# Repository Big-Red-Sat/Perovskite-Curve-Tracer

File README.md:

# Perovskite Curve Tracer
This project contains the hardware and software source for the curve tracer developed to evaluate perovskite solar cell samples during the [Big Red Sat-1 project](https://github.com/Big-Red-Sat/Big-Red-Sat-1).

## Hardware
The hardware is licensed under a CERN Open Hardware Licence Version 2 - Strongly Reciprocal license.  The developed hardware performs a passive curve tracing process that utilizes a low-Ohm resistor ladder, realized through analog switches and precision resistors.  The multiplexing of the perovskite solar cells is achieved through a low-Ohm analog SPDT relay.  Provisions are also made for an I2C connection to a temperature sensor on the sample holder.  A simple control interface is provisioned through USB for controlling the hardware and retrieve readings.

## Software
The software is licensed under an MIT license.  The software is operated using a single Python script under the software directory, `curve_tracer.py`.  
1. Clone this repository to a local directory,
2. Create a Python 3.9 virtual environment in the software folder,
3. Install all packages using the requirements.txt file,
4. Run curve_tracer.py.

## Performance
The collected data can be saved to the software folder under a directory called curves.  In that folder are numerous experiments from the Big Red Sat-1 project.  The plotted curves will look like the image below.

## Citation
If this repository was useful to your research, then please cite this repository using the BibTeX definition below.
```
@software{
  Arce_Perovskite_Curve_Tracer_2023,
  author = {Arce, Walker},
  month = aug,
  title = {{Perovskite Curve Tracer}},
  url = {https://github.com/wsarce/Perovskite-Curve-Tracer},
  version = {v1.0.0},
  year = {2023}
}
```
## Contact
For additional information or questions, please contact Walker Arce (wsarcera@gmail.com).

## License
The hardware is licensed under a CERN Open Hardware Licence Version 2 - Strongly Reciprocal, the software and firmware is licensed under an MIT license, and the documentation is licensed under a Creative Commons Attribution-ShareAlike 4.0 International Public License.

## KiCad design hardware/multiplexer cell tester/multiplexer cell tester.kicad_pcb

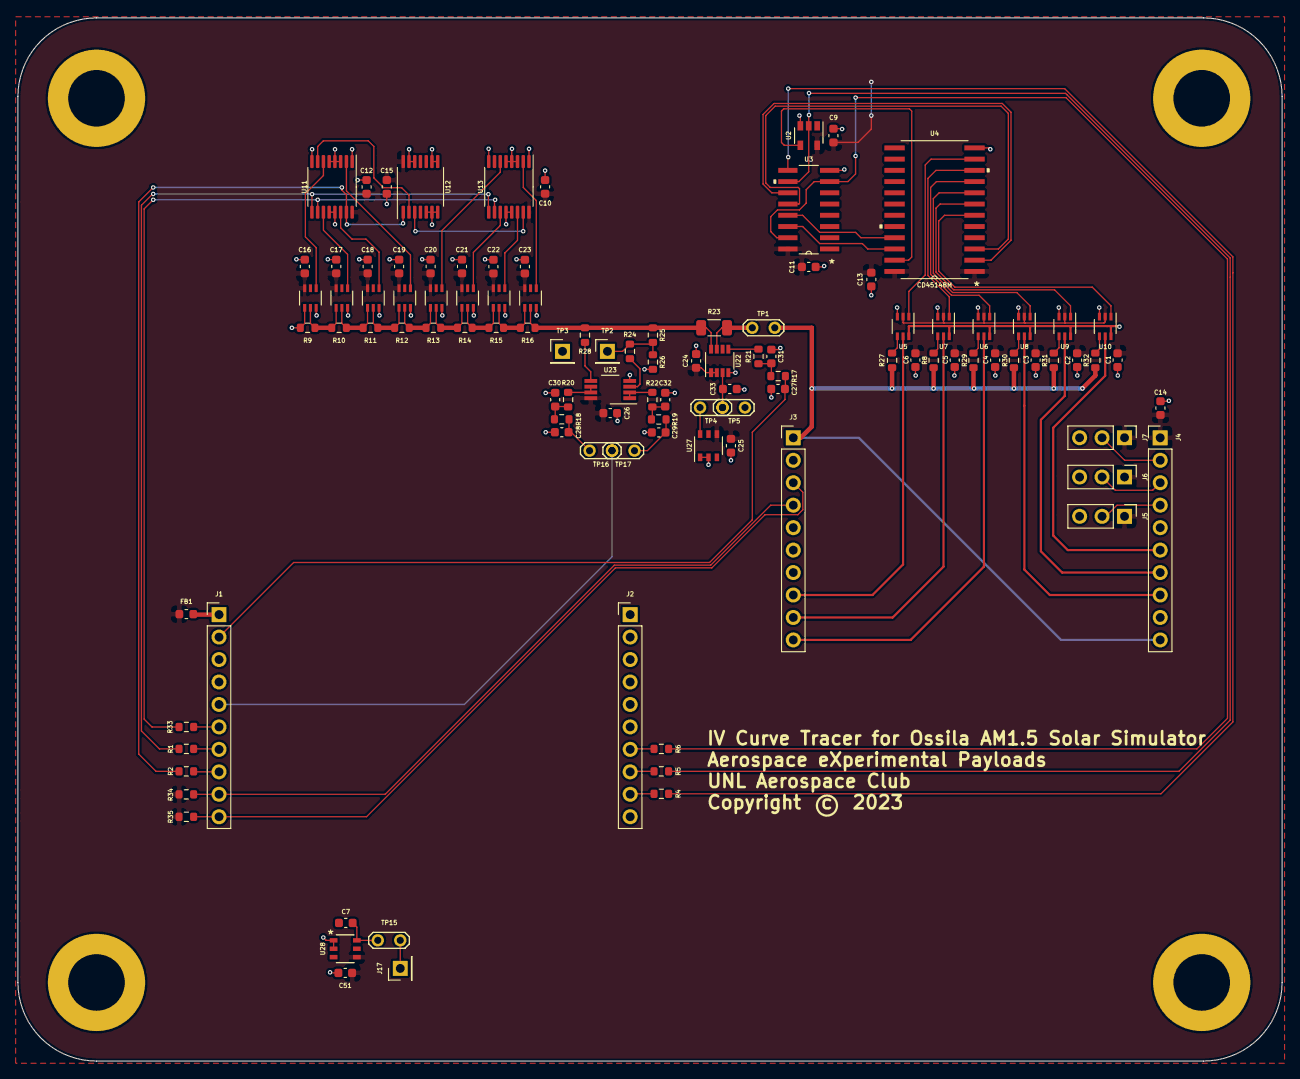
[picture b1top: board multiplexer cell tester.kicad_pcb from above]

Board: 2 copper layers, 143.0 x 118.0 mm, 107 parts (0 on the bottom side), 80 nets.

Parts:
C1, C2, C3, C4, C5, C6, C9, C10, C11, C12, C13, C14, C15, C16, C17, C18, C19, C20, C21, C22, C23, C24, C26, C51: 0.1u; C_0603_1608Metric
C7, C25, C33: 1u; C_0603_1608Metric
C27, C28, C29: 10n; C_0603_1608Metric
C30, C31, C32: 10u; C_0603_1608Metric
FB1: Ferrite_Bead; L_0603_1608Metric
J1, J2, J3, J4: Conn_01x10_Female; PinHeader_1x10_P2.54mm_Vertical
J5: A2 Select; PinHeader_1x03_P2.54mm_Vertical
J6: A1 Select; PinHeader_1x03_P2.54mm_Vertical
J7: A0 Select; PinHeader_1x03_P2.54mm_Vertical
J17: Conn_01x01_Male; PinHeader_1x01_P2.54mm_Vertical
R1, R2, R4, R5, R6, R33: 100; R_0603_1608Metric
R8, R27, R29, R30, R31, R32: 400; R_0603_1608Metric
R9: 50; R_0603_1608Metric
R10: 250; R_0603_1608Metric
R11: 500; R_0603_1608Metric
R12: 1000; R_0603_1608Metric
R13: 2000; R_0603_1608Metric
R14: 4000; R_0603_1608Metric
R15: 8000; R_0603_1608Metric
R16: 16000; R_0603_1608Metric
R17, R18, R19, R24, R28: 470; R_0603_1608Metric
R20, R21, R22: 10k; R_0603_1608Metric
R23: 510m; R_1206_3216Metric
R25, R26: 10M; R_0603_1608Metric
R34, R35: 4k7; R_0603_1608Metric
TP1, TP4, TP5, TP15, TP16, TP17: Current Test; TestPoint_2Pads_Pitch2.54mm_Drill0.8mm
TP2: Voltage Test+; PinHeader_1x01_P2.54mm_Vertical
TP3: Voltage Test-; PinHeader_1x01_P2.54mm_Vertical
U2: SN74LVC1G14DRL; SOT-23-5
U3: CD4518BM96
U4: CD4514BM
U5, U6, U7, U8, U9, U10: ADG839YKSZ-REEL7
U11, U13: CD4516B_PW_16; TSSOP-16_4.4x5mm_P0.65mm
U12: CD4071BE; TSSOP-14_4.4x5mm_P0.65mm
U14, U15, U16, U17, U18, U19, U20, U21: ADG841YKSZ-500RL7
U22: INA190A4IDDFR
U23: OPA2387; VSSOP-8_3.0x3.0mm_P0.65mm
U27: LT6654AMPS6-1.25; LT6654AMPS6-1.25-TRMPBF
U28: LT6654AHS6-3.3; LT6654AHS6-3.3-TRMPBF

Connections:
10-19_CLOCK: R4.2, U3.9
+3V3: C1.1, C2.1, C3.1, C4.1, C5.1, C6.1, C9.1, C10.1, C11.1, C12.1, C13.1, C14.1, C15.1, C16.1, C17.1, C18.1, C19.1, C20.1, C21.1, C22.1, C23.1, C24.1, C25.1, C26.1, C51.1, FB1.1, J4.1, J5.1, J6.1, J7.1, R34.1, R35.1, U2.5, U3.16, U4.1, U4.24, U5.2, U6.2, U7.2, U8.2, U9.2, U10.2, U11.16, U12.14, U13.16, U14.6, U15.6, U16.6, U17.6, U18.6, U19.6, U20.6, U21.6, U22.1, U22.2, U23.8, U27.4, U28.4
/Curve Tracer/LADDER_VOLTAGE: R16.1, R23.1, R25.2, R28.2, U21.2, U22.8
/Curve Tracer/PANEL_VOLTAGE: J3.1, J4.10, R8.1, R27.1, R29.1, R30.1, R31.1, R32.1, TP1.1
/Perovskite Switches/SCL: J1.9, J3.4, R34.2
/Perovskite Switches/SDA: J1.10, J3.3, R35.2
A0: J4.2, J7.2
A1: J4.3, J6.2
A2: J4.4, J5.2
ENABLE_PANEL_SWITCH: R5.1, U2.2, U3.10
GND: C1.2, C2.2, C3.2, C4.2, C5.2, C6.2, C7.2, C9.2, C10.2, C11.2, C12.2, C13.2, C14.2, C15.2, C16.2, C17.2, C18.2, C19.2, C20.2, C21.2, C22.2, C23.2, C24.2, C25.2, C26.2, C27.2, C28.2, C29.2, C30.2, C31.2, C32.2, C33.2, C51.2, J2.1, J3.6, J5.3, J6.3, J7.3, R9.2, R26.1, TP3.1, TP5.2, U2.3, U3.8, U4.12, U5.3, U5.6, U6.3, U6.6, U7.3, U7.6, U8.3, U8.6, U9.3, U9.6, U10.3, U10.6, U11.1, U11.3, U11.4, U11.5, U11.8, U11.12, U11.13, U12.5, U12.6, U12.7, U12.8, U12.9, U12.12, U12.13, U13.1, U13.3, U13.4, U13.5, U13.8, U13.12, U13.13, U14.1, U14.3, U15.3, U16.3, U17.3, U18.3, U19.3, U20.3, U21.3, U22.4, U23.4, U27.1, U27.2, U28.1, U28.2
LADDER_CLOCK: R2.2, U11.15, U12.1
LADDER_UD: R33.2, U11.10, U13.10
unnamed: C7.1, TP15.1, U28.6
unnamed: C28.1, R18.1, TP16.1
unnamed: C29.1, R19.1, TP17.1
unnamed: C30.1, R18.2, R20.1
unnamed: C31.1, R17.2, R21.1
unnamed: C32.1, R19.2, R22.1
unnamed: C33.1, TP4.1, TP5.1, U22.3
unnamed: FB1.2, J1.1
unnamed: J1.6, R33.1
unnamed: J1.7, R1.1
unnamed: J1.8, R2.1
unnamed: J2.7, R6.2
unnamed: J2.8, R5.2
unnamed: J2.9, R4.1
unnamed: J3.8, U5.5
unnamed: J3.9, U7.5
unnamed: J3.10, U6.5
unnamed: J4.6, U10.5
unnamed: J4.7, U9.5
unnamed: J4.8, U8.5
unnamed: J17.1, TP15.2
unnamed: R8.2, U7.4
unnamed: R10.1, R11.2, U15.2, U16.1
unnamed: R9.1, R10.2, U14.2, U15.1
unnamed: R11.1, R12.2, U16.2, U17.1
unnamed: R12.1, R13.2, U17.2, U18.1
unnamed: R13.1, R14.2, U18.2, U19.1
unnamed: R14.1, R15.2, U19.2, U20.1
unnamed: R15.1, R16.2, U20.2, U21.1
unnamed: R20.2, U23.6, U23.7
unnamed: R21.2, U22.5
unnamed: R22.2, U23.1, U23.2
unnamed: R23.2, TP1.2, U22.7
unnamed: R24.1, U23.3
unnamed: R24.2, R25.1, R26.2, TP2.1
unnamed: R27.2, U5.4
unnamed: R28.1, U23.5
unnamed: R29.2, U6.4
unnamed: R30.2, U8.4
unnamed: R31.2, U9.4
unnamed: R32.2, U10.4
unnamed: TP4.2, U27.6
unnamed: U2.4, U4.23
unnamed: U3.11, U4.2
unnamed: U3.12, U4.3
unnamed: U3.13, U4.21
unnamed: U3.14, U4.22
unnamed: U4.7, U9.1
unnamed: U4.8, U8.1
unnamed: U4.9, U6.1
unnamed: U4.10, U7.1
unnamed: U4.11, U5.1
unnamed: U4.6, U10.1
unnamed: U11.2, U17.4
unnamed: U11.6, U14.4
unnamed: U11.7, U12.2
unnamed: U11.11, U15.4
unnamed: U11.14, U16.4
unnamed: U12.3, U13.15
unnamed: U13.2, U21.4
unnamed: U13.6, U18.4
unnamed: U13.11, U19.4
unnamed: U13.14, U20.4
READ_CURRENT: C27.1, J1.2, R17.1
READ_VOLTAGE: J1.5, TP16.2, TP17.2
RESET_PANEL_SWITCH: R6.1, U3.7, U3.15
~LADDER_RESET: R1.2, U11.9, U13.9

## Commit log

2022-11-22 Add existing sources
2023-08-02 Update curve_tracer.py
    - Update for new curve tracer
    - Add current density conversion
    - Add folder selection and creation
2023-08-19 Update curve_tracer.py
    - Trace all pixels and show data on plot
    - Calculate other metrics
    - Find maximum power point
    - Export image of plot
2023-08-19 Add hardware and reorganize
2023-08-19 Create LICENSE
2023-08-19 Fix some bugs
    - Add epsilon to prevent divide by zero
    - Add power data
    - Fix xlsxwriter close
    - Make sure canvas updates during tracing
2023-08-19 Update licenses
2023-08-20 Add overall summary of panel
    - Concatenate all pixels summary data into a single spreadsheet
    - Add pictures of system
2023-08-20 Create step files for holder
2023-08-24 Updating curve tracer
    - Remove unused circuits
    - Update gerbers and renders
2023-09-08 Create holders
    - Created holders for the payload
    - Sliced holders for testing
2023-09-08 Update design to handle wire harnesses
2023-09-08 Add payload holder
    Added example of different holder for perovskites
2023-09-10 Finalized curve tracer
2023-10-05 Final testing
    - Finalize hardware, add output capacitor to voltage reference
    - Add curve data
    - Update curve tracing software to newest hardware
2023-10-09 Prefinal testing
    - 0.3NM torque tests
    - 0.7NM torque tests
    - Coverglass degredation tests
2023-10-12 Testing for A48 Problem
    - Disconnecting SDA and SCL fixed problem
2023-10-17 Tested final perovskites
2023-10-17 Move data into same folder
2023-10-17 Create folders for old data
2023-10-19 Tested final payloads
2023-11-05 Update curve results
2025-10-06 Working on paper
2025-10-31 Finish draft of paper
2025-10-31 Clean up
2026-03-28 Create figures

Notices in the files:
hardware/multiplexer cell tester/multiplexer cell tester.kicad_pcb:
Copyright (c) 2023
parts and their libraries:
Copyright 2016 Accelerated Designs. All rights reserved.
Copyright 2021 Accelerated Designs. All rights reserved.
